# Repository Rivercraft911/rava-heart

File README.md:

# Rava Heart

A heart-shaped PCB with 144 LEDs that syncs its heartbeat with a second one over ESP-NOW.
Put the two near each other and they beat together.

## Video

## What it does

- 144 WS2812B-MINI LEDs in two chains of 72, refreshed at 60 Hz
- Heartbeat mode: a slow double pulse, and shaking it adds an extra beat
- Gravity mode: red "liquid" sloshes around the heart as you tilt it
- Rainbow mode, because obviously
- Find Heart: a compass arrow (points north for now, eventually at the other heart)
- Hold the button for about a second and both hearts play "I ♥ U"
- When the two hearts are close enough they lock to the same beat

## Hardware

4-layer board, 94 × 88 mm, with an ESP32-C3, an accelerometer/gyro (LSM6DSOX) and a
magnetometer (LIS3MDL). Powered over USB-C, with an eFuse so 144 LEDs can't cook anything.

KiCad files are in [`hardware/`](hardware/), fab files in [`hardware/production/`](hardware/production/).

## Firmware

Builds with ESP-IDF 5.4+ or PlatformIO. Pin map, controls and build steps are in
[`firmware/README.md`](firmware/README.md).

There's also a browser simulator that runs the same effects with no hardware:
[`firmware/simulator/index.html`](firmware/simulator/).

## Other folders

- [`mechanical/`](mechanical/): scripts that generated the outline, placed the LEDs and routed power
- [`silkscreen_art/`](silkscreen_art/): how the back art was made

MIT licensed.

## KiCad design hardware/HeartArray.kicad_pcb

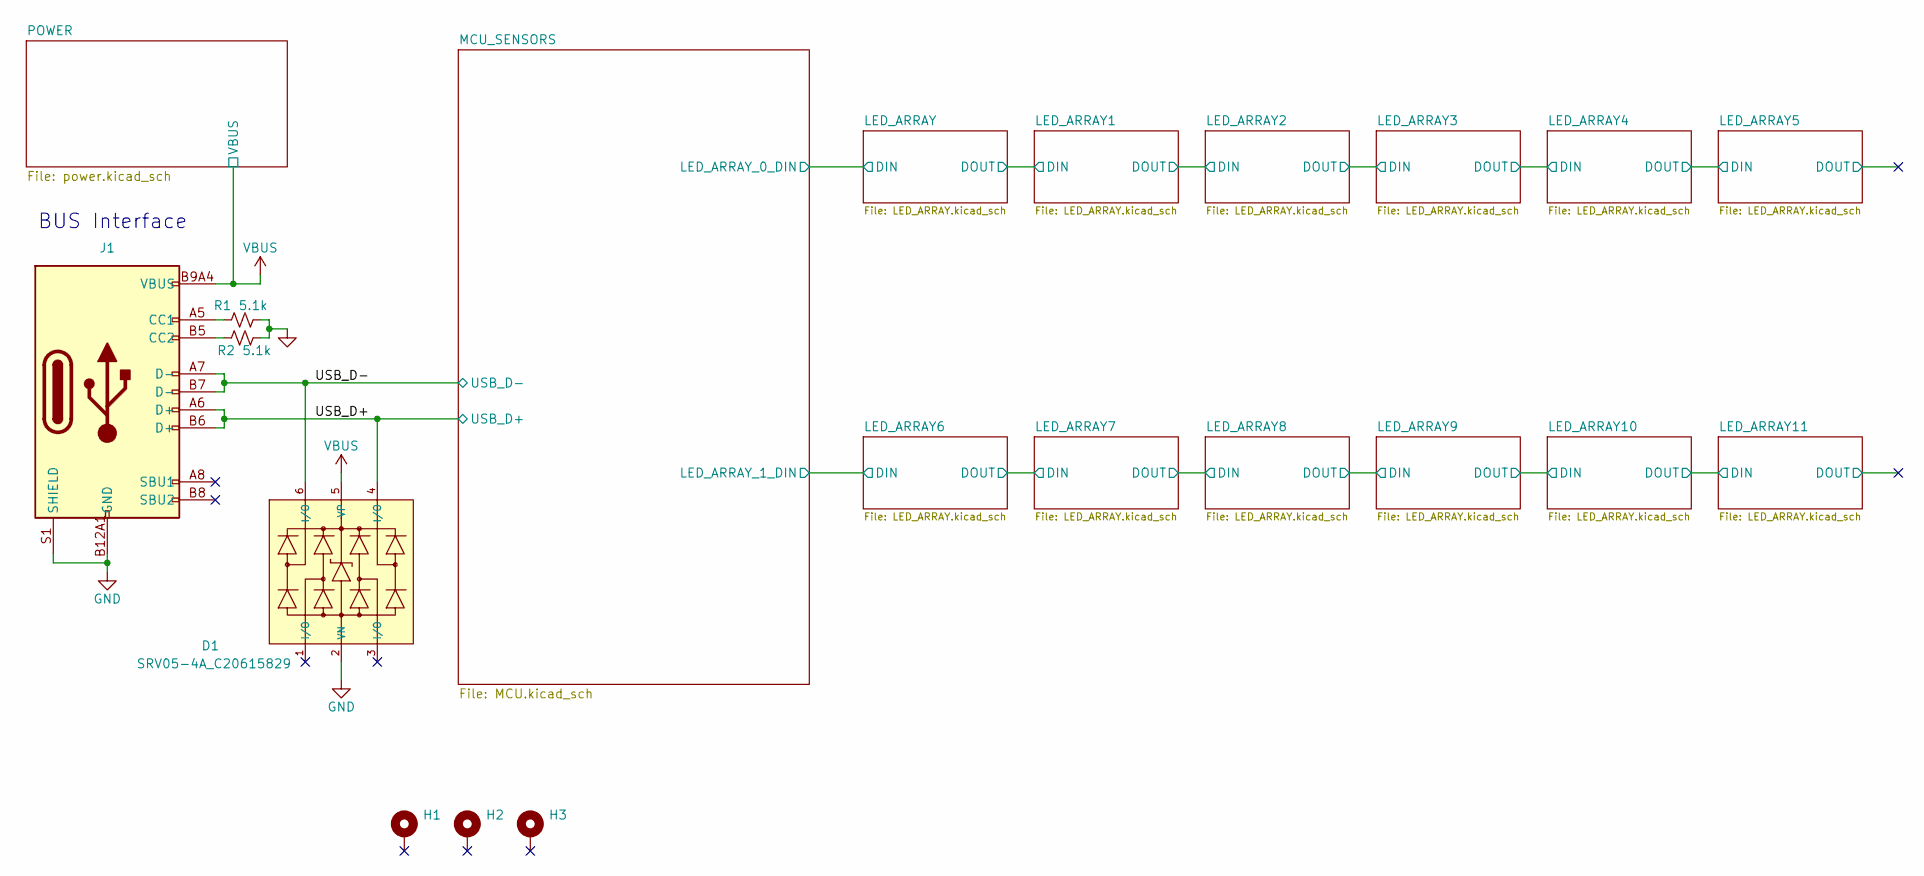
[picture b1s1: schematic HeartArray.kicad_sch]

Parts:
D1: SRV05-4A_C20615829; SOT-23-6_L2.9-W1.6-P0.95-LS2.9-BL; Part SRV05-4A; LCSC C20615829
H1, H2, H3: MountingHole_Pad; MountingHole_2.2mm_M2_DIN965_Pad
J1: Connector, USB-TYPE-C-16P; TYPE-C-SMD_HX-TYPE-C-16PIN; LCSC C2927039
R1, R2: 5.1k; R_0603_1608Metric; LCSC C23186

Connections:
/USB_D+: D1.4 (I/O), J1.A6 (D+), J1.B6 (D+); also elsewhere on the board
/USB_D-: D1.6 (I/O), J1.A7 (D-), J1.B7 (D-); also elsewhere on the board
GND: D1.2 (VN), J1.A12B1 (GND), J1.B12A1 (GND), J1.S1 (SHIELD), R1.2, R2.2; also elsewhere on the board
unnamed: J1.A5 (CC1), R1.1
unnamed: J1.B5 (CC2), R2.1
VBUS: D1.5 (VP), J1.A9B4 (VBUS), J1.B9A4 (VBUS); also elsewhere on the board

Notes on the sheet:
BUS Interface

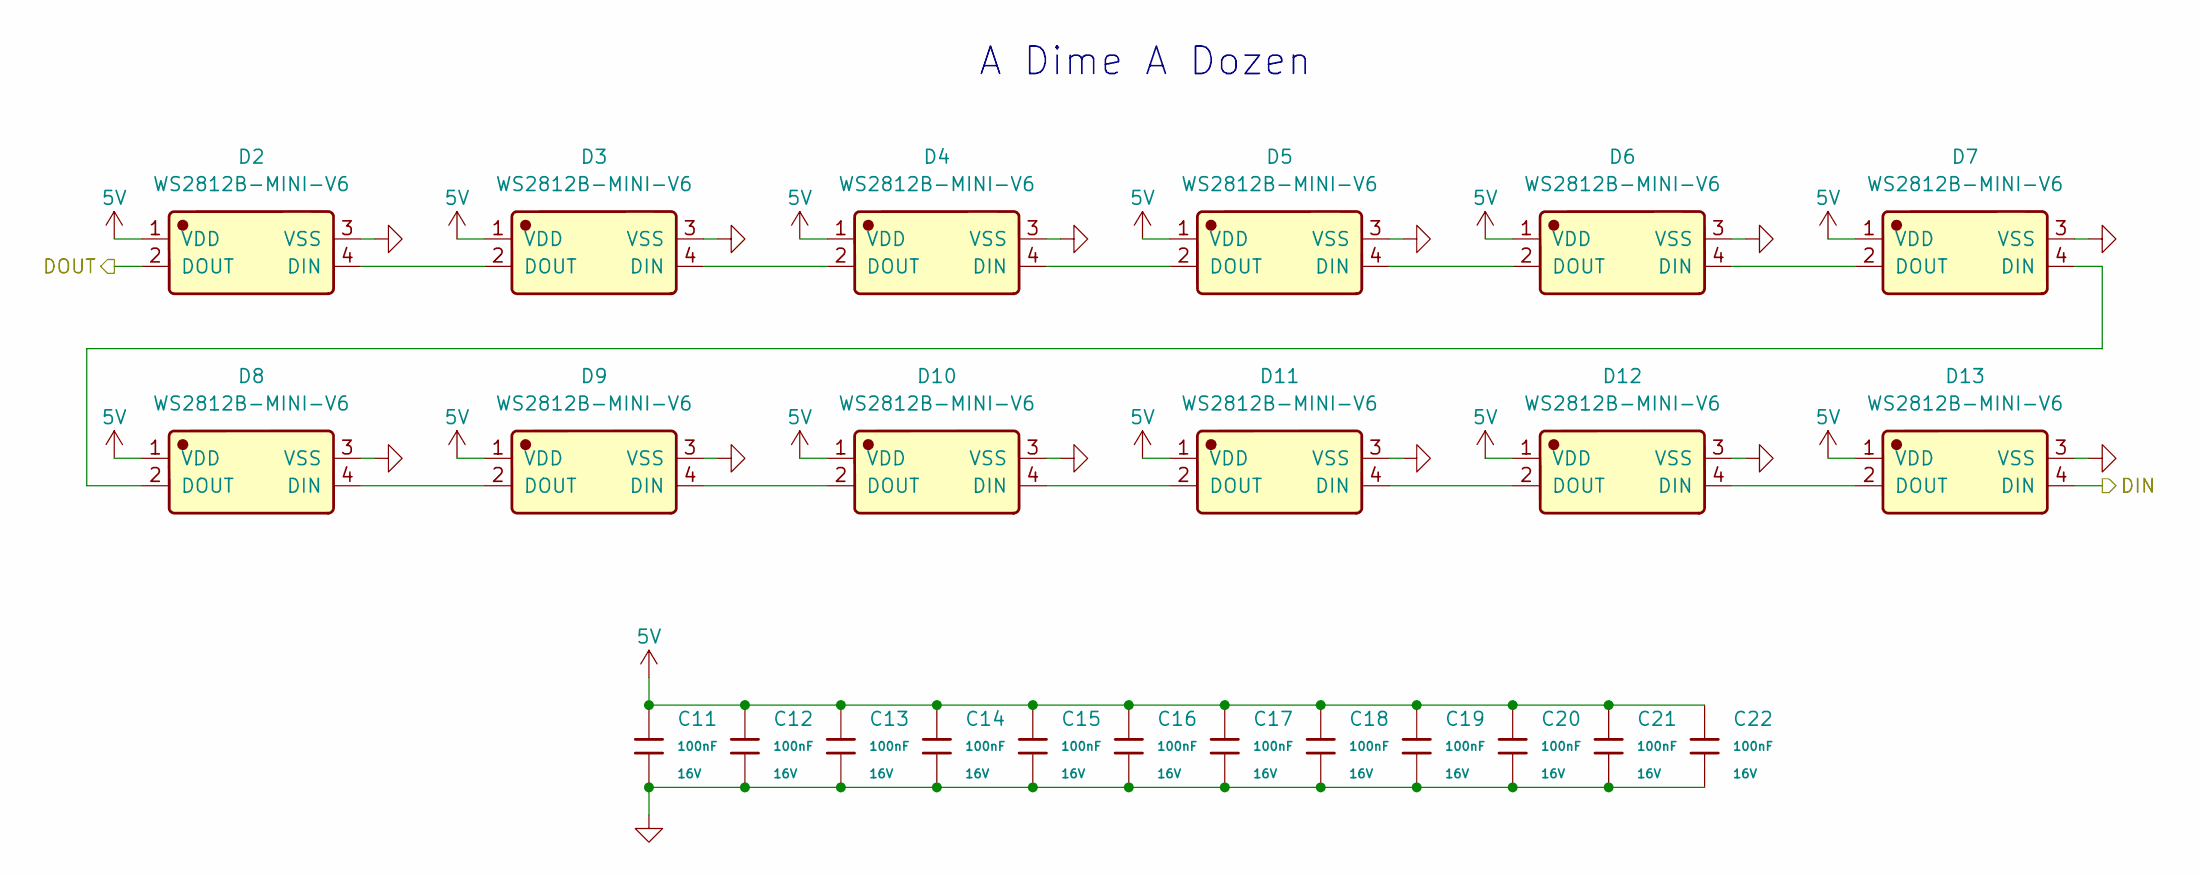
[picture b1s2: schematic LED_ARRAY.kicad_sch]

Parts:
C11, C12, C13, C14, C15, C16, C17, C18, C19, C20, C21, C22: 100nF; C_0402; Voltage Rated 16V; Tolerance ±10%; Part CL05B104KO5NNNC; LCSC C1525
D2, D3, D4, D5, D6, D7, D8, D9, D10, D11, D12, D13: WS2812B-MINI-V6; Manufacturer Part WS2812B-MINI-V6; LCSC C52941386

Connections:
5V: C11.1, C12.1, C13.1, C14.1, C15.1, C16.1, C17.1, C18.1, C19.1, C20.1, C21.1, C22.1, D2.1 (VDD), D3.1 (VDD), D4.1 (VDD), D5.1 (VDD), D6.1 (VDD), D7.1 (VDD), D8.1 (VDD), D9.1 (VDD), D10.1 (VDD), D11.1 (VDD), D12.1 (VDD), D13.1 (VDD); also elsewhere on the board
/LED_ARRAY/DIN: D13.4 (DIN); also elsewhere on the board
/LED_ARRAY/DOUT: D2.2 (DOUT); also elsewhere on the board
GND: C11.2, C12.2, C13.2, C14.2, C15.2, C16.2, C17.2, C18.2, C19.2, C20.2, C21.2, C22.2, D2.3 (VSS), D3.3 (VSS), D4.3 (VSS), D5.3 (VSS), D6.3 (VSS), D7.3 (VSS), D8.3 (VSS), D9.3 (VSS), D10.3 (VSS), D11.3 (VSS), D12.3 (VSS), D13.3 (VSS); also elsewhere on the board
unnamed: D2.4 (DIN), D3.2 (DOUT)
unnamed: D3.4 (DIN), D4.2 (DOUT)
unnamed: D4.4 (DIN), D5.2 (DOUT)
unnamed: D5.4 (DIN), D6.2 (DOUT)
unnamed: D6.4 (DIN), D7.2 (DOUT)
unnamed: D7.4 (DIN), D8.2 (DOUT)
unnamed: D8.4 (DIN), D9.2 (DOUT)
unnamed: D10.4 (DIN), D11.2 (DOUT)
unnamed: D9.4 (DIN), D10.2 (DOUT)
unnamed: D11.4 (DIN), D12.2 (DOUT)
unnamed: D12.4 (DIN), D13.2 (DOUT)

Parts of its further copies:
C33, C34, C35, C36, C37, C38, C39, C40, C41, C42, C43, C44, C45, C46, C47, C48, C49, C50, C51, C52, C53, C54, C55, C56, C57, C58, C59, C60, C61, C62, C63, C64, C65, C66, C67, C68, C69, C70, C71, C72, C73, C74, C75, C76, C77, C78, C79, C80, C81, C82, C83, C84, C85, C86, C87, C88, C89, C90, C91, C92, C93, C94, C95, C96, C97, C98, C99, C100, C101, C102, C103, C104, C105, C106, C107, C108, C109, C110, C111, C112, C113, C114, C115, C116, C117, C118, C119, C120, C121, C122, C123, C124, C125, C126, C127, C128, C129, C130, C131, C132, C133, C134, C135, C136, C137, C138, C139, C140, C141, C142, C143, C144, C145, C146, C147, C148, C149, C150, C151, C152, C153, C154, C155, C156, C157, C158, C159, C160, C161, C162, C163, C164: 100nF; C_0402; Voltage Rated 16V; Tolerance ±10%; Part CL05B104KO5NNNC; LCSC C1525
D14, D15, D16, D17, D18, D19, D20, D21, D22, D23, D24, D25, D26, D27, D28, D29, D30, D31, D32, D33, D34, D35, D36, D37, D38, D39, D40, D41, D42, D43, D44, D45, D46, D47, D48, D49, D50, D51, D52, D53, D54, D55, D56, D57, D58, D59, D60, D61, D62, D63, D64, D65, D66, D67, D68, D69, D70, D71, D72, D73, D74, D75, D76, D77, D78, D79, D80, D81, D82, D83, D84, D85, D86, D87, D88, D89, D90, D91, D92, D93, D94, D95, D96, D97, D98, D99, D100, D101, D102, D103, D104, D105, D106, D107, D108, D109, D110, D111, D112, D113, D114, D115, D116, D117, D118, D119, D120, D121, D122, D123, D124, D125, D126, D127, D128, D129, D130, D131, D132, D133, D134, D135, D136, D137, D138, D139, D140, D141, D142, D143, D144, D145: WS2812B-MINI-V6; Manufacturer Part WS2812B-MINI-V6; LCSC C52941386

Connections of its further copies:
5V: C33.1, C34.1, C35.1, C36.1, C37.1, C38.1, C39.1, C40.1, C41.1, C42.1, C43.1, C44.1, C45.1, C46.1, C47.1, C48.1, C49.1, C50.1, C51.1, C52.1, C53.1, C54.1, C55.1, C56.1, C57.1, C58.1, C59.1, C60.1, C61.1, C62.1, C63.1, C64.1, C65.1, C66.1, C67.1, C68.1, C69.1, C70.1, C71.1, C72.1, C73.1, C74.1, C75.1, C76.1, C77.1, C78.1, C79.1, C80.1, C81.1, C82.1, C83.1, C84.1, C85.1, C86.1, C87.1, C88.1, C89.1, C90.1, C91.1, C92.1, C93.1, C94.1, C95.1, C96.1, C97.1, C98.1, C99.1, C100.1, C101.1, C102.1, C103.1, C104.1, C105.1, C106.1, C107.1, C108.1, C109.1, C110.1, C111.1, C112.1, C113.1, C114.1, C115.1, C116.1, C117.1, C118.1, C119.1, C120.1, C121.1, C122.1, C123.1, C124.1, C125.1, C126.1, C127.1, C128.1, C129.1, C130.1, C131.1, C132.1, C133.1, C134.1, C135.1, C136.1, C137.1, C138.1, C139.1, C140.1, C141.1, C142.1, C143.1, C144.1, C145.1, C146.1, C147.1, C148.1, C149.1, C150.1, C151.1, C152.1, C153.1, C154.1, C155.1, C156.1, C157.1, C158.1, C159.1, C160.1, C161.1, C162.1, C163.1, C164.1, D14.1 (VDD), D15.1 (VDD), D16.1 (VDD), D17.1 (VDD), D18.1 (VDD), D19.1 (VDD), D20.1 (VDD), D21.1 (VDD), D22.1 (VDD), D23.1 (VDD), D24.1 (VDD), D25.1 (VDD), D26.1 (VDD), D27.1 (VDD), D28.1 (VDD), D29.1 (VDD), D30.1 (VDD), D31.1 (VDD), D32.1 (VDD), D33.1 (VDD), D34.1 (VDD), D35.1 (VDD), D36.1 (VDD), D37.1 (VDD), D38.1 (VDD), D39.1 (VDD), D40.1 (VDD), D41.1 (VDD), D42.1 (VDD), D43.1 (VDD), D44.1 (VDD), D45.1 (VDD), D46.1 (VDD), D47.1 (VDD), D48.1 (VDD), D49.1 (VDD), D50.1 (VDD), D51.1 (VDD), D52.1 (VDD), D53.1 (VDD), D54.1 (VDD), D55.1 (VDD), D56.1 (VDD), D57.1 (VDD), D58.1 (VDD), D59.1 (VDD), D60.1 (VDD), D61.1 (VDD), D62.1 (VDD), D63.1 (VDD), D64.1 (VDD), D65.1 (VDD), D66.1 (VDD), D67.1 (VDD), D68.1 (VDD), D69.1 (VDD), D70.1 (VDD), D71.1 (VDD), D72.1 (VDD), D73.1 (VDD), D74.1 (VDD), D75.1 (VDD), D76.1 (VDD), D77.1 (VDD), D78.1 (VDD), D79.1 (VDD), D80.1 (VDD), D81.1 (VDD), D82.1 (VDD), D83.1 (VDD), D84.1 (VDD), D85.1 (VDD), D86.1 (VDD), D87.1 (VDD), D88.1 (VDD), D89.1 (VDD), D90.1 (VDD), D91.1 (VDD), D92.1 (VDD), D93.1 (VDD), D94.1 (VDD), D95.1 (VDD), D96.1 (VDD), D97.1 (VDD), D98.1 (VDD), D99.1 (VDD), D100.1 (VDD), D101.1 (VDD), D102.1 (VDD), D103.1 (VDD), D104.1 (VDD), D105.1 (VDD), D106.1 (VDD), D107.1 (VDD), D108.1 (VDD), D109.1 (VDD), D110.1 (VDD), D111.1 (VDD), D112.1 (VDD), D113.1 (VDD), D114.1 (VDD), D115.1 (VDD), D116.1 (VDD), D117.1 (VDD), D118.1 (VDD), D119.1 (VDD), D120.1 (VDD), D121.1 (VDD), D122.1 (VDD), D123.1 (VDD), D124.1 (VDD), D125.1 (VDD), D126.1 (VDD), D127.1 (VDD), D128.1 (VDD), D129.1 (VDD), D130.1 (VDD), D131.1 (VDD), D132.1 (VDD), D133.1 (VDD), D134.1 (VDD), D135.1 (VDD), D136.1 (VDD), D137.1 (VDD), D138.1 (VDD), D139.1 (VDD), D140.1 (VDD), D141.1 (VDD), D142.1 (VDD), D143.1 (VDD), D144.1 (VDD), D145.1 (VDD); also elsewhere on the board
/LED_ARRAY1/DOUT: D14.2 (DOUT), D37.4 (DIN)
/LED_ARRAY2/DOUT: D26.2 (DOUT), D49.4 (DIN)
/LED_ARRAY3/DOUT: D38.2 (DOUT), D61.4 (DIN)
/LED_ARRAY4/DOUT: D50.2 (DOUT), D73.4 (DIN)
/LED_ARRAY5/DOUT: D62.2 (DOUT)
/LED_ARRAY6/DIN: D85.4 (DIN); also elsewhere on the board
/LED_ARRAY6/DOUT: D74.2 (DOUT), D97.4 (DIN)
/LED_ARRAY7/DOUT: D86.2 (DOUT), D109.4 (DIN)
/LED_ARRAY8/DOUT: D98.2 (DOUT), D121.4 (DIN)
/LED_ARRAY10/DIN: D110.2 (DOUT), D133.4 (DIN)
/LED_ARRAY10/DOUT: D122.2 (DOUT), D145.4 (DIN)
/LED_ARRAY11/DOUT: D134.2 (DOUT)
/LED_ARRAY/DOUT: D25.4 (DIN); also elsewhere on the board
GND: C33.2, C34.2, C35.2, C36.2, C37.2, C38.2, C39.2, C40.2, C41.2, C42.2, C43.2, C44.2, C45.2, C46.2, C47.2, C48.2, C49.2, C50.2, C51.2, C52.2, C53.2, C54.2, C55.2, C56.2, C57.2, C58.2, C59.2, C60.2, C61.2, C62.2, C63.2, C64.2, C65.2, C66.2, C67.2, C68.2, C69.2, C70.2, C71.2, C72.2, C73.2, C74.2, C75.2, C76.2, C77.2, C78.2, C79.2, C80.2, C81.2, C82.2, C83.2, C84.2, C85.2, C86.2, C87.2, C88.2, C89.2, C90.2, C91.2, C92.2, C93.2, C94.2, C95.2, C96.2, C97.2, C98.2, C99.2, C100.2, C101.2, C102.2, C103.2, C104.2, C105.2, C106.2, C107.2, C108.2, C109.2, C110.2, C111.2, C112.2, C113.2, C114.2, C115.2, C116.2, C117.2, C118.2, C119.2, C120.2, C121.2, C122.2, C123.2, C124.2, C125.2, C126.2, C127.2, C128.2, C129.2, C130.2, C131.2, C132.2, C133.2, C134.2, C135.2, C136.2, C137.2, C138.2, C139.2, C140.2, C141.2, C142.2, C143.2, C144.2, C145.2, C146.2, C147.2, C148.2, C149.2, C150.2, C151.2, C152.2, C153.2, C154.2, C155.2, C156.2, C157.2, C158.2, C159.2, C160.2, C161.2, C162.2, C163.2, C164.2, D14.3 (VSS), D15.3 (VSS), D16.3 (VSS), D17.3 (VSS), D18.3 (VSS), D19.3 (VSS), D20.3 (VSS), D21.3 (VSS), D22.3 (VSS), D23.3 (VSS), D24.3 (VSS), D25.3 (VSS), D26.3 (VSS), D27.3 (VSS), D28.3 (VSS), D29.3 (VSS), D30.3 (VSS), D31.3 (VSS), D32.3 (VSS), D33.3 (VSS), D34.3 (VSS), D35.3 (VSS), D36.3 (VSS), D37.3 (VSS), D38.3 (VSS), D39.3 (VSS), D40.3 (VSS), D41.3 (VSS), D42.3 (VSS), D43.3 (VSS), D44.3 (VSS), D45.3 (VSS), D46.3 (VSS), D47.3 (VSS), D48.3 (VSS), D49.3 (VSS), D50.3 (VSS), D51.3 (VSS), D52.3 (VSS), D53.3 (VSS), D54.3 (VSS), D55.3 (VSS), D56.3 (VSS), D57.3 (VSS), D58.3 (VSS), D59.3 (VSS), D60.3 (VSS), D61.3 (VSS), D62.3 (VSS), D63.3 (VSS), D64.3 (VSS), D65.3 (VSS), D66.3 (VSS), D67.3 (VSS), D68.3 (VSS), D69.3 (VSS), D70.3 (VSS), D71.3 (VSS), D72.3 (VSS), D73.3 (VSS), D74.3 (VSS), D75.3 (VSS), D76.3 (VSS), D77.3 (VSS), D78.3 (VSS), D79.3 (VSS), D80.3 (VSS), D81.3 (VSS), D82.3 (VSS), D83.3 (VSS), D84.3 (VSS), D85.3 (VSS), D86.3 (VSS), D87.3 (VSS), D88.3 (VSS), D89.3 (VSS), D90.3 (VSS), D91.3 (VSS), D92.3 (VSS), D93.3 (VSS), D94.3 (VSS), D95.3 (VSS), D96.3 (VSS), D97.3 (VSS), D98.3 (VSS), D99.3 (VSS), D100.3 (VSS), D101.3 (VSS), D102.3 (VSS), D103.3 (VSS), D104.3 (VSS), D105.3 (VSS), D106.3 (VSS), D107.3 (VSS), D108.3 (VSS), D109.3 (VSS), D110.3 (VSS), D111.3 (VSS), D112.3 (VSS), D113.3 (VSS), D114.3 (VSS), D115.3 (VSS), D116.3 (VSS), D117.3 (VSS), D118.3 (VSS), D119.3 (VSS), D120.3 (VSS), D121.3 (VSS), D122.3 (VSS), D123.3 (VSS), D124.3 (VSS), D125.3 (VSS), D126.3 (VSS), D127.3 (VSS), D128.3 (VSS), D129.3 (VSS), D130.3 (VSS), D131.3 (VSS), D132.3 (VSS), D133.3 (VSS), D134.3 (VSS), D135.3 (VSS), D136.3 (VSS), D137.3 (VSS), D138.3 (VSS), D139.3 (VSS), D140.3 (VSS), D141.3 (VSS), D142.3 (VSS), D143.3 (VSS), D144.3 (VSS), D145.3 (VSS); also elsewhere on the board
unnamed: D14.4 (DIN), D15.2 (DOUT)
unnamed: D15.4 (DIN), D16.2 (DOUT)
unnamed: D16.4 (DIN), D17.2 (DOUT)
unnamed: D17.4 (DIN), D18.2 (DOUT)
unnamed: D18.4 (DIN), D19.2 (DOUT)
unnamed: D19.4 (DIN), D20.2 (DOUT)
unnamed: D20.4 (DIN), D21.2 (DOUT)
unnamed: D21.4 (DIN), D22.2 (DOUT)
unnamed: D22.4 (DIN), D23.2 (DOUT)
unnamed: D23.4 (DIN), D24.2 (DOUT)
unnamed: D24.4 (DIN), D25.2 (DOUT)
unnamed: D26.4 (DIN), D27.2 (DOUT)
unnamed: D27.4 (DIN), D28.2 (DOUT)
unnamed: D28.4 (DIN), D29.2 (DOUT)
unnamed: D29.4 (DIN), D30.2 (DOUT)
unnamed: D30.4 (DIN), D31.2 (DOUT)
unnamed: D31.4 (DIN), D32.2 (DOUT)
unnamed: D32.4 (DIN), D33.2 (DOUT)
unnamed: D33.4 (DIN), D34.2 (DOUT)
unnamed: D34.4 (DIN), D35.2 (DOUT)
unnamed: D35.4 (DIN), D36.2 (DOUT)
unnamed: D36.4 (DIN), D37.2 (DOUT)
unnamed: D38.4 (DIN), D39.2 (DOUT)
unnamed: D39.4 (DIN), D40.2 (DOUT)
unnamed: D40.4 (DIN), D41.2 (DOUT)
unnamed: D41.4 (DIN), D42.2 (DOUT)
unnamed: D42.4 (DIN), D43.2 (DOUT)
unnamed: D43.4 (DIN), D44.2 (DOUT)
unnamed: D44.4 (DIN), D45.2 (DOUT)
unnamed: D45.4 (DIN), D46.2 (DOUT)
unnamed: D46.4 (DIN), D47.2 (DOUT)
unnamed: D47.4 (DIN), D48.2 (DOUT)
unnamed: D48.4 (DIN), D49.2 (DOUT)
unnamed: D50.4 (DIN), D51.2 (DOUT)
unnamed: D51.4 (DIN), D52.2 (DOUT)
unnamed: D52.4 (DIN), D53.2 (DOUT)
unnamed: D53.4 (DIN), D54.2 (DOUT)
unnamed: D54.4 (DIN), D55.2 (DOUT)
unnamed: D55.4 (DIN), D56.2 (DOUT)
unnamed: D56.4 (DIN), D57.2 (DOUT)
unnamed: D57.4 (DIN), D58.2 (DOUT)
unnamed: D58.4 (DIN), D59.2 (DOUT)
unnamed: D59.4 (DIN), D60.2 (DOUT)
unnamed: D60.4 (DIN), D61.2 (DOUT)
unnamed: D62.4 (DIN), D63.2 (DOUT)
unnamed: D63.4 (DIN), D64.2 (DOUT)
unnamed: D64.4 (DIN), D65.2 (DOUT)
unnamed: D65.4 (DIN), D66.2 (DOUT)
unnamed: D66.4 (DIN), D67.2 (DOUT)
unnamed: D67.4 (DIN), D68.2 (DOUT)
unnamed: D68.4 (DIN), D69.2 (DOUT)
unnamed: D69.4 (DIN), D70.2 (DOUT)
unnamed: D70.4 (DIN), D71.2 (DOUT)
unnamed: D71.4 (DIN), D72.2 (DOUT)
unnamed: D72.4 (DIN), D73.2 (DOUT)
unnamed: D74.4 (DIN), D75.2 (DOUT)
unnamed: D75.4 (DIN), D76.2 (DOUT)
unnamed: D76.4 (DIN), D77.2 (DOUT)
unnamed: D77.4 (DIN), D78.2 (DOUT)
unnamed: D78.4 (DIN), D79.2 (DOUT)
unnamed: D79.4 (DIN), D80.2 (DOUT)
unnamed: D80.4 (DIN), D81.2 (DOUT)
unnamed: D81.4 (DIN), D82.2 (DOUT)
unnamed: D82.4 (DIN), D83.2 (DOUT)
unnamed: D83.4 (DIN), D84.2 (DOUT)
unnamed: D84.4 (DIN), D85.2 (DOUT)
unnamed: D86.4 (DIN), D87.2 (DOUT)
unnamed: D87.4 (DIN), D88.2 (DOUT)
unnamed: D88.4 (DIN), D89.2 (DOUT)
unnamed: D89.4 (DIN), D90.2 (DOUT)
unnamed: D90.4 (DIN), D91.2 (DOUT)
unnamed: D91.4 (DIN), D92.2 (DOUT)
unnamed: D92.4 (DIN), D93.2 (DOUT)
unnamed: D93.4 (DIN), D94.2 (DOUT)
unnamed: D94.4 (DIN), D95.2 (DOUT)
unnamed: D95.4 (DIN), D96.2 (DOUT)
unnamed: D96.4 (DIN), D97.2 (DOUT)
unnamed: D98.4 (DIN), D99.2 (DOUT)
unnamed: D100.4 (DIN), D101.2 (DOUT)
unnamed: D99.4 (DIN), D100.2 (DOUT)
unnamed: D101.4 (DIN), D102.2 (DOUT)
unnamed: D102.4 (DIN), D103.2 (DOUT)
unnamed: D103.4 (DIN), D104.2 (DOUT)
unnamed: D104.4 (DIN), D105.2 (DOUT)
unnamed: D105.4 (DIN), D106.2 (DOUT)
unnamed: D106.4 (DIN), D107.2 (DOUT)
unnamed: D107.4 (DIN), D108.2 (DOUT)
unnamed: D108.4 (DIN), D109.2 (DOUT)
unnamed: D110.4 (DIN), D111.2 (DOUT)
unnamed: D111.4 (DIN), D112.2 (DOUT)
unnamed: D112.4 (DIN), D113.2 (DOUT)
unnamed: D113.4 (DIN), D114.2 (DOUT)
unnamed: D114.4 (DIN), D115.2 (DOUT)
unnamed: D115.4 (DIN), D116.2 (DOUT)
unnamed: D116.4 (DIN), D117.2 (DOUT)
unnamed: D117.4 (DIN), D118.2 (DOUT)
unnamed: D118.4 (DIN), D119.2 (DOUT)
unnamed: D119.4 (DIN), D120.2 (DOUT)
unnamed: D120.4 (DIN), D121.2 (DOUT)
unnamed: D122.4 (DIN), D123.2 (DOUT)
unnamed: D123.4 (DIN), D124.2 (DOUT)
unnamed: D124.4 (DIN), D125.2 (DOUT)
unnamed: D125.4 (DIN), D126.2 (DOUT)
unnamed: D126.4 (DIN), D127.2 (DOUT)
unnamed: D127.4 (DIN), D128.2 (DOUT)
unnamed: D128.4 (DIN), D129.2 (DOUT)
unnamed: D129.4 (DIN), D130.2 (DOUT)
unnamed: D130.4 (DIN), D131.2 (DOUT)
unnamed: D131.4 (DIN), D132.2 (DOUT)
unnamed: D132.4 (DIN), D133.2 (DOUT)
unnamed: D134.4 (DIN), D135.2 (DOUT)
unnamed: D135.4 (DIN), D136.2 (DOUT)
unnamed: D136.4 (DIN), D137.2 (DOUT)
unnamed: D137.4 (DIN), D138.2 (DOUT)
unnamed: D138.4 (DIN), D139.2 (DOUT)
unnamed: D139.4 (DIN), D140.2 (DOUT)
unnamed: D140.4 (DIN), D141.2 (DOUT)
unnamed: D141.4 (DIN), D142.2 (DOUT)
unnamed: D142.4 (DIN), D143.2 (DOUT)
unnamed: D143.4 (DIN), D144.2 (DOUT)
unnamed: D144.4 (DIN), D145.2 (DOUT)

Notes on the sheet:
A Dime A Dozen

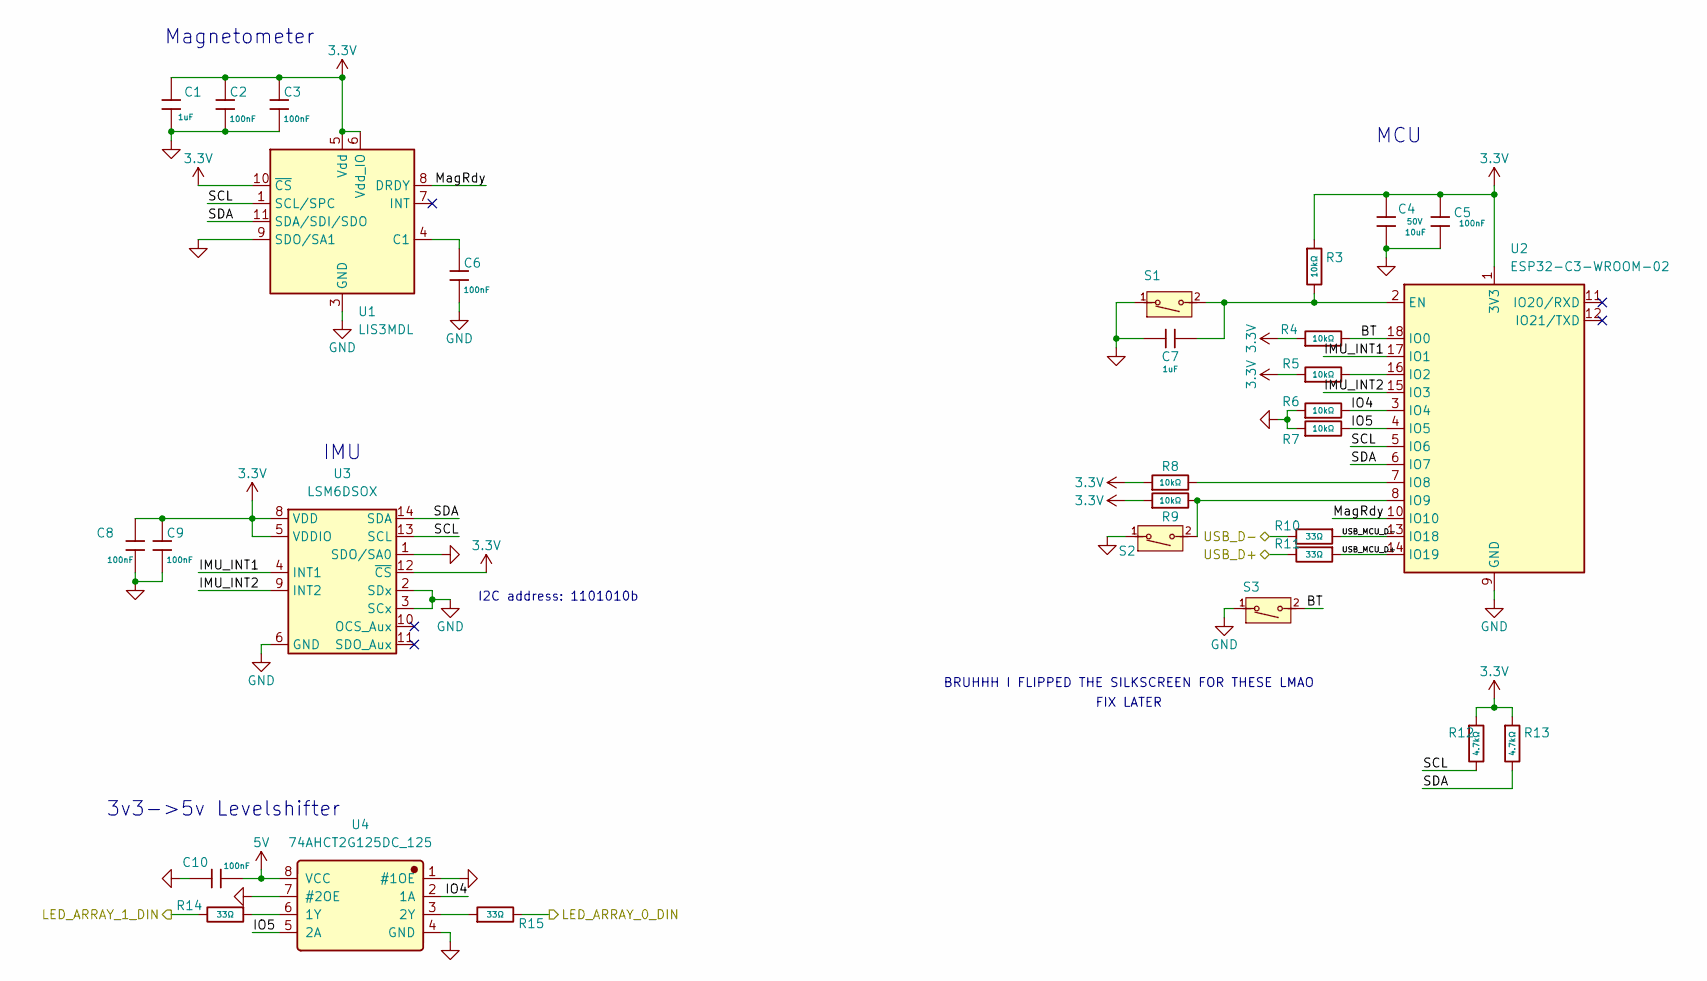
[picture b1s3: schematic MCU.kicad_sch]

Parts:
C1, C7: 1uF; C_0603; Voltage Rated 50V; Tolerance ±10%; Part CL10A105KB8NNNC; LCSC C15849
C2, C3, C5, C6, C8, C9, C10: 100nF; C_0402; Voltage Rated 16V; Tolerance ±10%; Part CL05B104KO5NNNC; LCSC C1525
C4: 10uF; C_1206; Voltage Rated 50V; Tolerance ±10%; Part CL31A106KBHNNNE; LCSC C13585
R3, R4, R5, R6, R7, R8, R9: 10kΩ; R_0402; Overload Voltage (Max) 50V; Tolerance ±1%; Part 0402WGF1002TCE; LCSC C25744
R10, R11, R14, R15: 33Ω; R_0402; Overload Voltage (Max) 50V; Tolerance ±1%; Part 0402WGF330JTCE; LCSC C25105
R12, R13: 4.7kΩ; R_0402; Overload Voltage (Max) 50V; Tolerance ±1%; Part 0402WGF4701TCE; LCSC C25900
S1, S2, S3: Tactile Button, 160gf; SW_TS-1088-AR02016; Voltage Rating (Dc) 12V; Part TS-1088-AR02016; LCSC C720477
U1: LIS3MDL; LGA-12_2x2mm_P0.5mm; LCSC C478483
U2: ESP32-C3-WROOM-02; LCSC C2934560
U3: LSM6DSOX; ST_LGA-14L_2.5x3.0mm_P0.5mm_4x3; LCSC C481766
U4: 74AHCT2G125DC_125; Manufacturer Part 74AHCT2G125DC,125; LCSC C554633

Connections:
3.3V: C1.1, C2.1, C3.1, C4.1, C5.1, C8.1, C9.1, R3.1, R4.1, R5.1, R8.1, R9.1, R12.1, R13.1, U1.5 (Vdd), U1.6 (Vdd_IO), U1.10 (~CS), U2.1 (3V3), U3.5 (VDDIO), U3.8 (VDD), U3.12 (~CS); also elsewhere on the board
5V: C10.2, U4.8 (VCC); also elsewhere on the board
/LED_ARRAY6/DIN: R14.2; also elsewhere on the board
/LED_ARRAY/DIN: R15.2; also elsewhere on the board
/MCU_SENSORS/BT: R4.2, S3.2 (B), U2.18 (IO0)
/MCU_SENSORS/IMU_INT1: U2.17 (IO1), U3.4 (INT1)
/MCU_SENSORS/IMU_INT2: U2.15 (IO3), U3.9 (INT2)
/MCU_SENSORS/IO4: R6.2, U2.3 (IO4), U4.2 (1A)
/MCU_SENSORS/IO5: R7.2, U2.4 (IO5), U4.5 (2A)
/MCU_SENSORS/MagRdy: U1.8 (DRDY), U2.10 (IO10)
/MCU_SENSORS/SCL: R12.2, U1.1 (SCL/SPC), U2.5 (IO6), U3.13 (SCL)
/MCU_SENSORS/SDA: R13.2, U1.11 (SDA/SDI/SDO), U2.6 (IO7), U3.14 (SDA)
/MCU_SENSORS/USB_MCU_D+: R11.1, U2.14 (IO19)
/MCU_SENSORS/USB_MCU_D-: R10.1, U2.13 (IO18)
/USB_D+: R11.2; also elsewhere on the board
/USB_D-: R10.2; also elsewhere on the board
GND: C1.2, C2.2, C3.2, C4.2, C5.2, C6.2, C7.2, C8.2, C9.2, C10.1, R6.1, R7.1, S1.1 (A), S2.1 (A), S3.1 (A), U1.2 (GND), U1.3 (GND), U1.9 (SDO/SA1), U1.12 (GND), U2.9 (GND), U2.19 (GND), U3.1 (SDO/SA0), U3.2 (SDx), U3.3 (SCx), U3.6 (GND), U3.7 (GND), U4.1 (#1OE), U4.4 (GND), U4.7 (#2OE); also elsewhere on the board
unnamed: C7.1, R3.2, S1.2 (B), U2.2 (EN)
unnamed: R9.2, S2.2 (B), U2.8 (IO9)
unnamed: C6.1, U1.4 (C1)
unnamed: R5.2, U2.16 (IO2)
unnamed: R8.2, U2.7 (IO8)
unnamed: R14.1, U4.6 (1Y)
unnamed: R15.1, U4.3 (2Y)

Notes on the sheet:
IMU
I2C address: 1101010b
BRUHHH I FLIPPED THE SILKSCREEN FOR THESE LMAO
FIX LATER
MCU
Magnetometer
3v3->5v Levelshifter

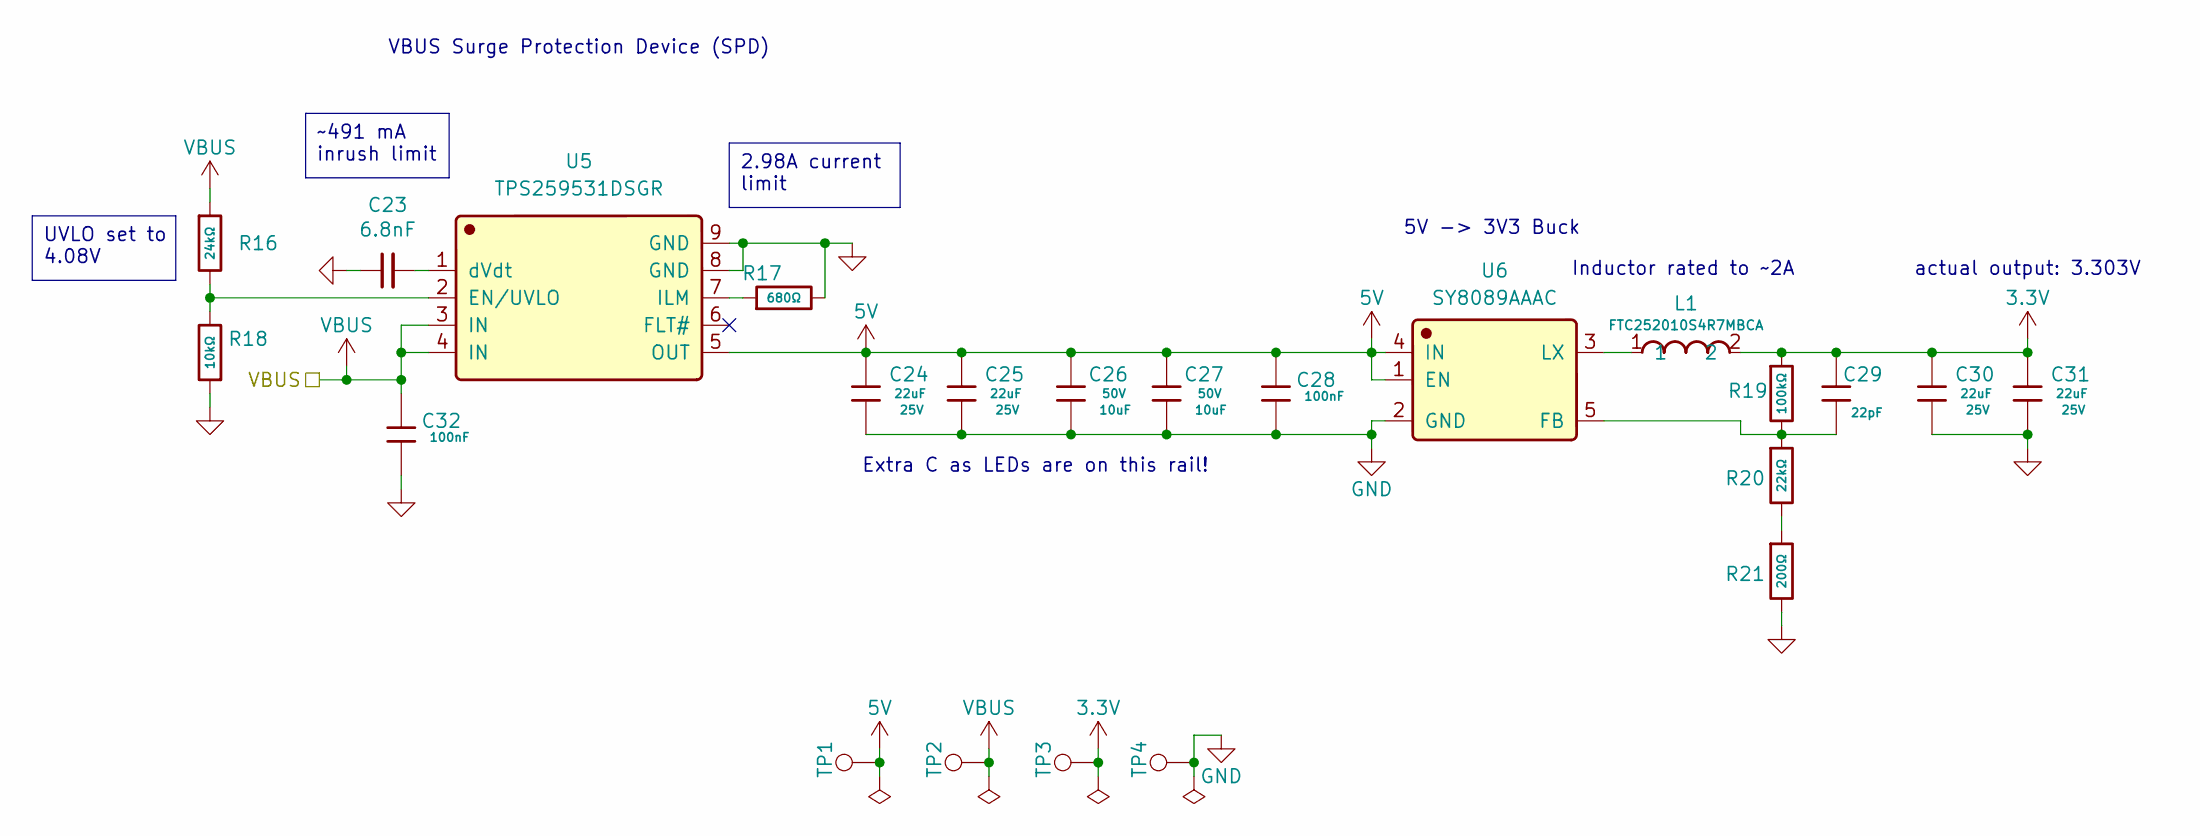
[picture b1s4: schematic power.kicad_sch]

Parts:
C23: 6.8nF; C_0603_1608Metric; Voltage 50V; Tolerance 5%; LCSC C307492
C24, C25, C30, C31: 22uF; C_1206; Voltage Rated 25V; Tolerance ±10%; Part CL31A226KAHNNNE; LCSC C12891
C26, C27: 10uF; C_1206; Voltage Rated 50V; Tolerance ±10%; Part CL31A106KBHNNNE; LCSC C13585
C28, C32: 100nF; C_0402; Voltage Rated 16V; Tolerance ±10%; Part CL05B104KO5NNNC; LCSC C1525
C29: 22pF; C_0402; Voltage Rated 50V; Tolerance ±5%; Part 0402CG220J500NT; LCSC C1555
L1: FTC252010S4R7MBCA; Manufacturer Part FTC252010S4R7MBCA; LCSC C5832360
R16: 24kΩ; R_0402; Overload Voltage (Max) 50V; Tolerance ±1%; Part 0402WGF2402TCE; LCSC C25769
R17: 680Ω; R_0402; Overload Voltage (Max) 50V; Tolerance ±1%; Part 0402WGF6800TCE; LCSC C25130
R18: 10kΩ; R_0402; Overload Voltage (Max) 50V; Tolerance ±1%; Part 0402WGF1002TCE; LCSC C25744
R19: 100kΩ; R_0402; Overload Voltage (Max) 50V; Tolerance ±1%; Part 0402WGF1003TCE; LCSC C25741
R20: 22kΩ; R_0402; Overload Voltage (Max) 50V; Tolerance ±1%; Part 0402WGF2202TCE; LCSC C25768
R21: 200Ω; R_0402; Overload Voltage (Max) 50V; Tolerance ±1%; Part 0402WGF2000TCE; LCSC C25087
TP1: 5V; TestPoint_Pad_1.5x1.5mm
TP2, TP3, TP4: TestPoint_Pad_1.5x1.5mm
U5: TPS259531DSGR; Manufacturer Part TPS259531DSGR; LCSC C2155674
U6: SY8089AAAC; Manufacturer Part SY8089AAAC; LCSC C78988

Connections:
3.3V: C29.1, C30.1, C31.1, L1.2, R19.1, TP3.1 (1_1); also elsewhere on the board
5V: C24.1, C25.1, C26.1, C27.1, C28.1, TP1.1 (1_1), U5.5 (OUT), U6.1 (EN), U6.4 (IN); also elsewhere on the board
GND: C23.1, C24.2, C25.2, C26.2, C27.2, C28.2, C30.2, C31.2, C32.2, R17.2, R18.1, R21.2, TP4.1 (1_1), U5.8 (GND), U5.9 (GND), U6.2 (GND); also elsewhere on the board
unnamed: R20.2, R21.1
unnamed: R16.2, R18.2, U5.2 (EN/UVLO)
unnamed: R17.1, U5.7 (ILM)
unnamed: C23.2, U5.1 (dVdt)
unnamed: C29.2, R19.2, R20.1, U6.5 (FB)
unnamed: L1.1, U6.3 (LX)
VBUS: C32.1, R16.1, TP2.1 (1_1), U5.3 (IN), U5.4 (IN); also elsewhere on the board

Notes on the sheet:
Extra C as LEDs are on this rail!
5V -> 3V3 Buck
actual output: 3.303V
VBUS Surge Protection Device (SPD)
Inductor rated to ~2A
~491 mA inrush limit
UVLO set to 4.08V
2.98A current limit

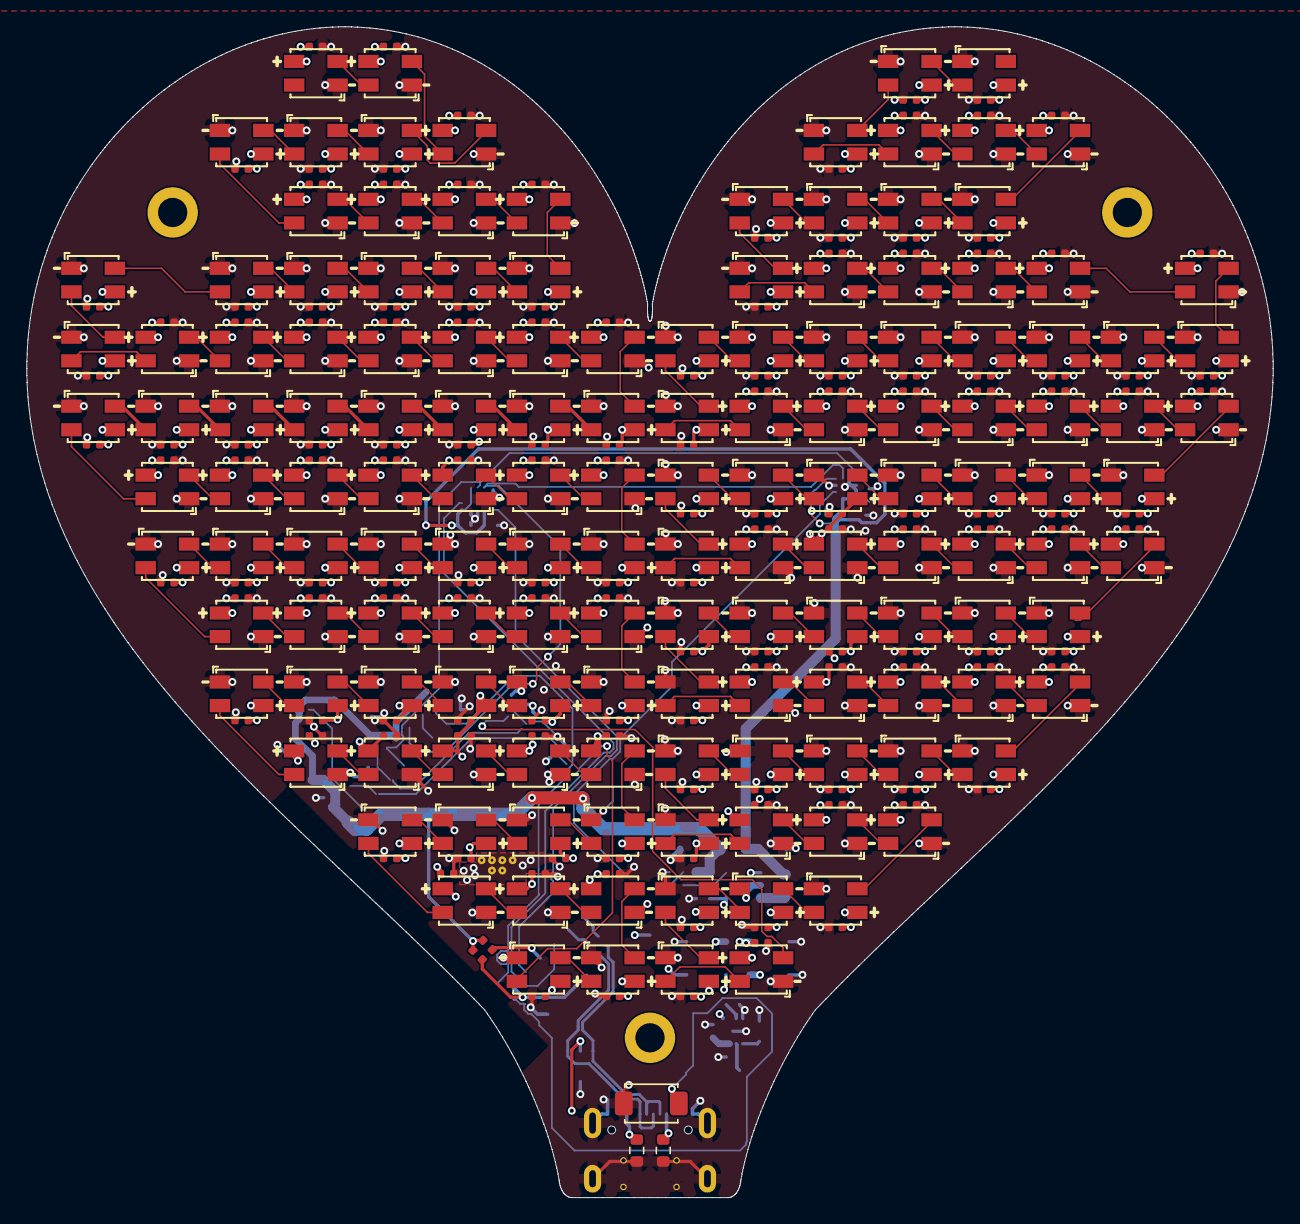
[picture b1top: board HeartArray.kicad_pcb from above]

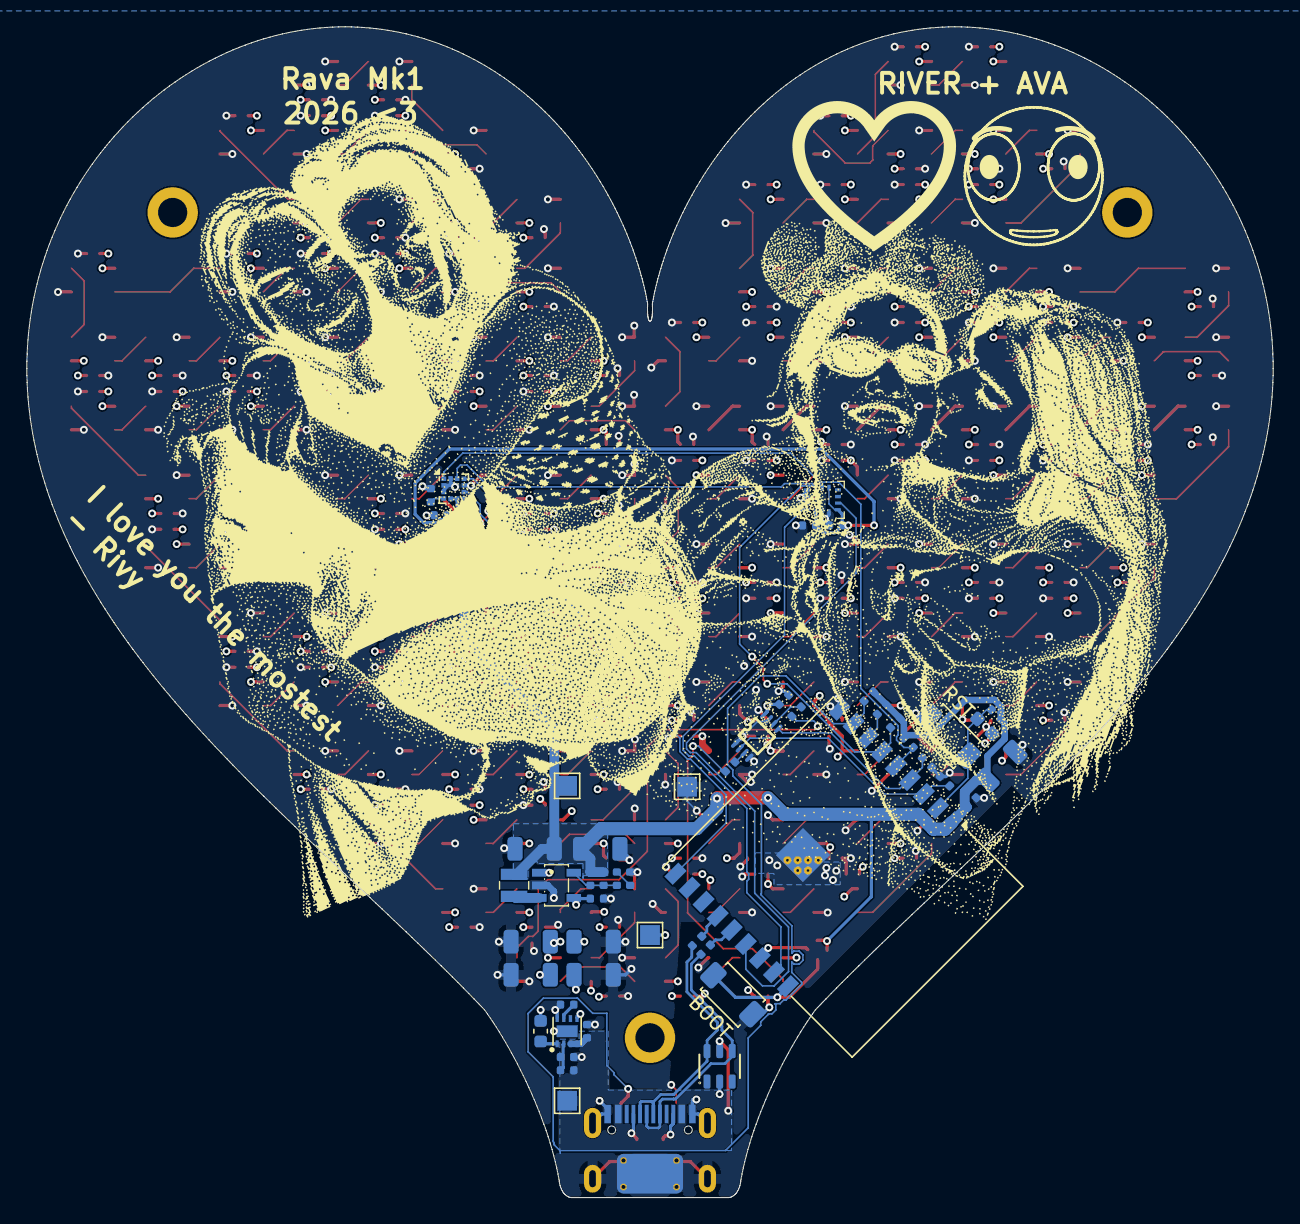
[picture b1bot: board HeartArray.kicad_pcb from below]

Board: 4 copper layers, 94.0 x 88.3 mm, 348 parts (52 on the bottom side), 175 nets.

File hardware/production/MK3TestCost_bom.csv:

Designator,Footprint,Quantity,Value,LCSC Part #
"C1, C7",C_0603,2,1uF,C15849
"C10, C100, C101, C102, C103, C104, C105, C106, C107, C108, C109, C11, C110, C111, C112, C113, C114, C115, C116, C117, C118, C119, C12, C120, C121, C122, C123, C124, C125, C126, C127, C128, C129, C13, C130, C131, C132, C133, C134, C135, C136, C137, C138, C139, C14, C140, C141, C142, C143, C144, C145, C146, C147, C148, C149, C15, C150, C151, C152, C153, C154, C155, C156, C157, C158, C159, C16, C160, C161, C162, C163, C164, C17, C18, C19, C2, C20, C21, C22, C28, C3, C32, C33, C34, C35, C36, C37, C38, C39, C40, C41, C42, C43, C44, C45, C46, C47, C48, C49, C5, C50, C51, C52, C53, C54, C55, C56, C57, C58, C59, C6, C60, C61, C62, C63, C64, C65, C66, C67, C68, C69, C70, C71, C72, C73, C74, C75, C76, C77, C78, C79, C8, C80, C81, C82, C83, C84, C85, C86, C87, C88, C89, C9, C90, C91, C92, C93, C94, C95, C96, C97, C98, C99",C_0402,153,100nF,C1525
C23,0603,1,6.8nF,C307492
"C24, C25, C30, C31",C_1206,4,22uF,C12891
"C26, C27, C4",C_1206,3,10uF,C13585
C29,C_0402,1,22pF,C1555
D1,SOT-23-6_L2.9-W1.6-P0.95-LS2.9-BL,1,SRV05-4A_C20615829,C20615829
"D10, D100, D101, D102, D103, D104, D105, D106, D107, D108, D109, D11, D110, D111, D112, D113, D114, D115, D116, D117, D118, D119, D12, D120, D121, D122, D123, D124, D125, D126, D127, D128, D129, D13, D130, D131, D132, D133, D134, D135, D136, D137, D138, D139, D14, D140, D141, D142, D143, D144, D145, D15, D16, D17, D18, D19, D2, D20, D21, D22, D23, D24, D25, D26, D27, D28, D29, D3, D30, D31, D32, D33, D34, D35, D36, D37, D38, D39, D4, D40, D41, D42, D43, D44, D45, D46, D47, D48, D49, D5, D50, D51, D52, D53, D54, D55, D56, D57, D58, D59, D6, D60, D61, D62, D63, D64, D65, D66, D67, D68, D69, D7, D70, D71, D72, D73, D74, D75, D76, D77, D78, D79, D8, D80, D81, D82, D83, D84, D85, D86, D87, D88, D89, D9, D90, D91, D92, D93, D94, D95, D96, D97, D98, D99",WS2812B-MINI-V6,144,WS2812B-MINI-V6,C52941386
J1,TYPE-C-SMD_HX-TYPE-C-16PIN,1,"Connector, USB-TYPE-C-16P",C2927039
L1,FTC252010S4R7MBCA,1,FTC252010S4R7MBCA,C5832360
"R1, R2",0603,2,5.1k,C23186
"R10, R11, R14, R15",R_0402,4,33Ω,C25105
"R12, R13",R_0402,2,4.7kΩ,C25900
R16,R_0402,1,24kΩ,C25769
R17,R_0402,1,680Ω,C25130
"R18, R3, R4, R5, R6, R7, R8, R9",R_0402,8,10kΩ,C25744
R19,R_0402,1,100kΩ,C25741
R20,R_0402,1,22kΩ,C25768
R21,R_0402,1,200Ω,C25087
"S1, S2, S3",SW_TS-1088-AR02016,3,"Tactile Button, 160gf",C720477
TP1,TestPoint_Pad_1.5x1.5mm,1,5V,
"TP2, TP3, TP4",TestPoint_Pad_1.5x1.5mm,3,~,
U1,LGA-12_2x2mm_P0.5mm,1,LIS3MDL,C478483
U2,ESP32-C3-WROOM-02,1,ESP32-C3-WROOM-02,C2934560
U3,ST_LGA-14L_2.5x3.0mm_P0.5mm_4x3,1,LSM6DSOX,C481766
U4,74AHCT2G125DC_125,1,74AHCT2G125DC_125,C554633
U5,TPS259531DSGR,1,TPS259531DSGR,C2155674
U6,SY8089AAAC,1,SY8089AAAC,C78988
